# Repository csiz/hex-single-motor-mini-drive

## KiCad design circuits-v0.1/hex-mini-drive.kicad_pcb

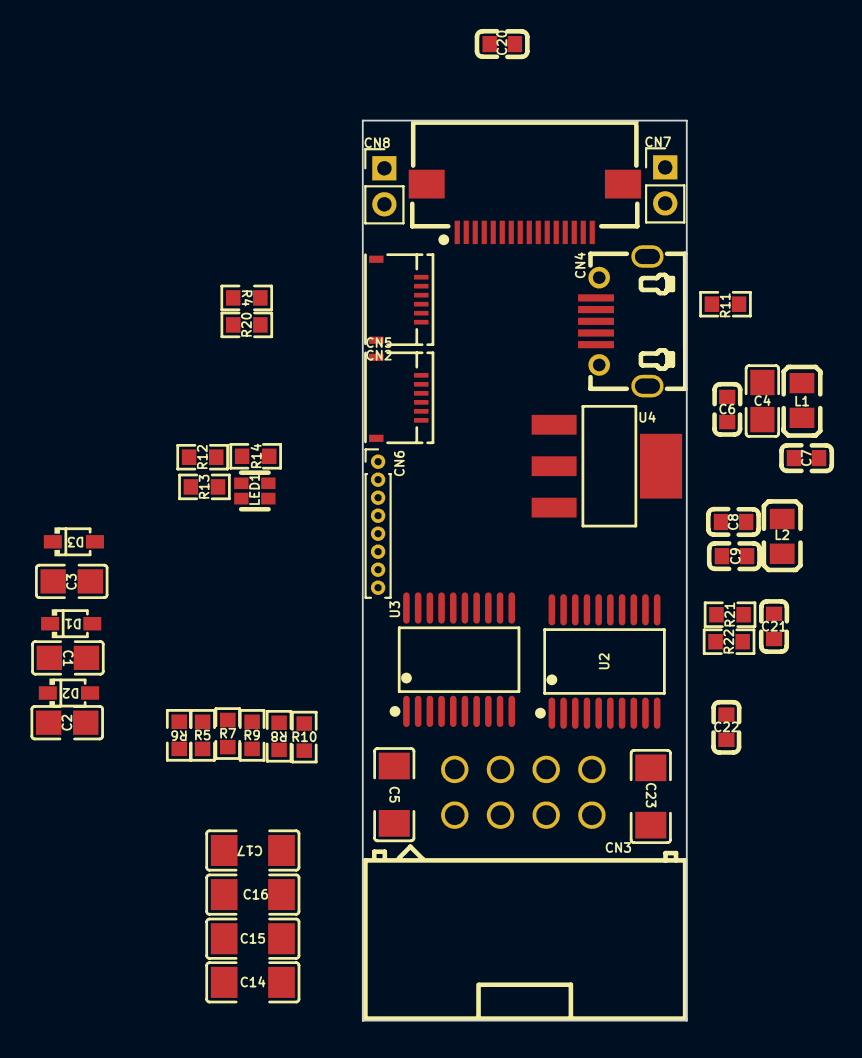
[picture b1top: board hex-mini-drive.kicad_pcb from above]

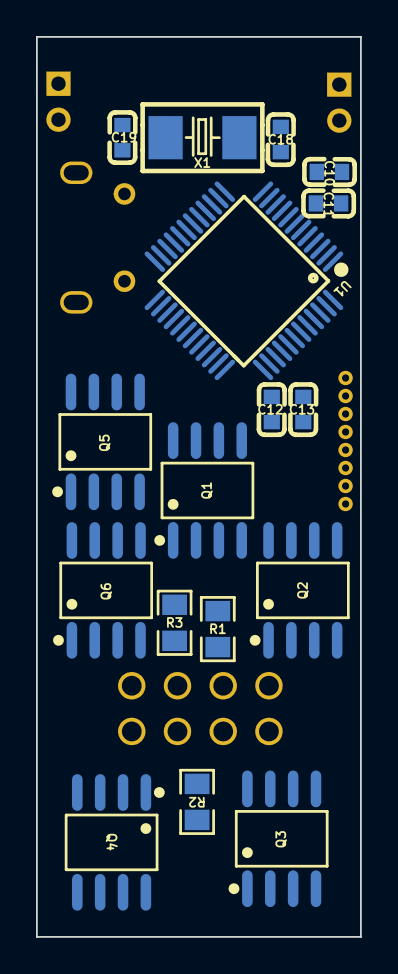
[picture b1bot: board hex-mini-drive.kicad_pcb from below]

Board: 4 copper layers, 18.0 x 50.0 mm, 65 parts (17 on the bottom side), 69 nets, no tracks yet.

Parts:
C1, C2, C3: 10nF; C0805
C4: 0.1uF; C0805
C5, C14, C15, C16, C17, C23: 10uF; C1206
C6, C7, C9: 1uF; C0603
C8, C10, C11, C12, C13, C20, C21, C22: 100nF; C0603
C18, C19: 30pF; C0603
CN1: FPC-SMD_P0.50-16P_FGS-XJ-H2.0
CN2, CN5: FPC-SMD_6P-P0.50_L3.8-W5.0
CN3: IDC-TH_8P-P2.54-H-R2-C4-S2.54
CN4: MICRO-USB-SMD_MICRONJ5P-1.0-1.25
CN6: Conn_01x08_Pin; PinHeader_1x08_P1.00mm_Vertical
CN7, CN8: Conn_01x02_Pin; PinHeader_1x02_P2.00mm_Vertical
D1, D2, D3: IN4148WS T4 SOD-323_L1.8-W1.3-LS2.5-RD
L1: 300mΩ; L0805
L2: 10uH; L0805
LED1: LED-ARRAY-SMD_4P-L1.6-W1.5-BR_XL-1615RGBC-RF
Q1, Q2, Q3, Q4, Q5, Q6: AO4266E SOIC-8_L4.9-W3.9-P1.27-LS6.0-BL
R1, R2, R3: 500mW 10mΩ; R0805
R4: 100kΩ; R0603
R5, R6, R7, R8, R9, R10: 10Ω; R0603
R11, R12, R13, R14: 1.5kΩ; R0603
R20: 10kΩ; R0603
R21, R22: 47kΩ; R0603
U1: STM32F103C8T6 LQFP-48_L7.0-W7.0-P0.50-LS9.0-BL
U2: INA4181A1 TSSOP-20_L6.5-W4.4-P0.65-LS6.4-BL
U3: FD6288T TSSOP-20_L6.5-W4.4-P0.65-LS6.4-BL
U4: AMS1117-3.3 SOT-223-3_L6.5-W3.4-P2.30-LS7.0-BR
X1: CRYSTAL-SMD_L5.0-W3.2

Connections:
+3V3: C6.2, C10.2, C11.2, C12.2, C13.2, C22.2, CN2.1, CN3.5, CN5.1, L2.1, LED1.2 (COM+), R11.2, U1.1 (VBAT), U1.24 (VDD_1), U1.36 (VDD_2), U1.48 (VDD_3), U2.5 (VS), U4.2 (VOUT)
+3V3A: C8.2, C9.2, L2.2, R21.2, U1.9 (VDDA)
+5V: CN1.1, CN4.1 (VCC), L1.2
+VDC: C4.2, C5.2, C14.1, C15.1, C16.1, C17.1, C23.1, CN1.12, CN1.13, CN1.14, CN1.15, CN1.16, CN7.2, CN8.2, D1.2 (A), D2.2 (A), D3.2 (A), Q1.5 (D), Q1.6 (D), Q1.7 (D), Q1.8 (D), Q3.5 (D), Q3.6 (D), Q3.7 (D), Q3.8 (D), Q5.5 (D), Q5.6 (D), Q5.7 (D), Q5.8 (D), R4.2, U3.7 (VCC)
/Boost Gate 1: C1.2, D1.1 (K), U3.20 (VB1)
/Boost Gate 2: C2.2, D2.1 (K), U3.17 (VB2)
/Boost Gate 3: C3.2, D3.1 (K), U3.14 (VB3)
/Filtered +5V: C7.2, L1.1, U4.3 (VIN)
/HO1: R5.1, U3.19 (HO1)
/HO2: R9.1, U3.16 (HO2)
/HO3: R10.1, U3.13 (HO3)
/LO1: R6.1, U3.11 (LO1)
/LO2: R7.2, U3.10 (LO2)
/LO3: R8.2, U3.9 (LO3)
/RCC_OSC_IN: C18.2, U1.5 (PD0-OSC_IN), X1.1 (OSC1)
/RCC_OSC_OUT: C19.2, U1.6 (PD1-OSC_OUT), X1.2 (OSC2)
ADC1_IN2: U1.12 (PA2), U2.2 (OUT1)
ADC1_IN3: U1.13 (PA3), U2.8 (OUT2)
ADC1_IN4: U1.14 (PA4), U2.13 (OUT3)
ADC1_IN5/REF: C21.2, R21.1, R22.2, U1.15 (PA5), U2.1 (REF1), U2.9 (REF2), U2.12 (REF3), U2.20 (REF4)
ADC1_IN6: R4.1, R20.2, U1.16 (PA6)
BOOT0: CN1.5, U1.44 (BOOT0)
GATE1H: Q1.4 (G), R5.2
GATE1L: Q2.4 (G), R6.2
GATE2H: Q3.4 (G), R9.2
GATE2L: Q4.4 (G), R7.1
GATE3H: Q5.4 (G), R10.2
GATE3L: Q6.4 (G), R8.1
GND: C4.1, C5.1, C6.1, C7.1, C8.1, C9.1, C10.1, C11.1, C12.1, C13.1, C14.2, C15.2, C16.2, C17.2, C18.1, C19.1, C20.1, C21.1, C22.1, C23.2, CN1.7, CN1.8, CN1.9, CN1.10, CN1.11, CN2.2, CN3.4, CN4.5 (GND), CN5.2, CN6.1, CN7.1, CN8.1, Q2.1 (S), Q2.2 (S), Q2.3 (S), Q4.1 (S), Q4.2 (S), Q4.3 (S), Q6.1 (S), Q6.2 (S), Q6.3 (S), R20.1, R22.1, U1.8 (VSSA), U1.23 (VSS_1), U1.35 (VSS_2), U1.47 (VSS_3), U2.16 (GND), U3.8 (COM), U4.1 (GND)
GPIO_Input_A: CN5.5, CN6.6, U1.2 (PC13-TAMPER-RTC)
GPIO_Input_B: CN5.6, CN6.7, U1.3 (PC14-OSC32_IN)
GPIO_Input_C: CN6.8, U1.4 (PC15-OSC32_OUT)
GPIO_Input_CS: CN1.4, U1.20 (PB2)
I2C1_SCL: CN5.4, U1.45 (PB8)
I2C1_SDA: CN5.3, U1.46 (PB9)
NRST: C20.2, CN1.6, U1.7 (NRST)
unnamed: LED1.3 (B-), R13.2
unnamed: LED1.4 (G-), R12.2
unnamed: LED1.1 (R-), R14.1
OUT1: C1.1, CN3.6, R1.2, U2.4 (IN+1), U3.18 (VS1)
OUT2: C2.1, CN3.7, R2.2, U2.7 (IN±2), U3.15 (VS2)
OUT3: C3.1, CN3.8, R3.2, U2.15 (IN+3), U3.12 (VS3)
SHUNT1: Q1.1 (S), Q1.2 (S), Q1.3 (S), Q2.5 (D), Q2.6 (D), Q2.7 (D), Q2.8 (D), R1.1, U2.3 (IN±1)
SHUNT2: Q3.1 (S), Q3.2 (S), Q3.3 (S), Q4.5 (D), Q4.6 (D), Q4.7 (D), Q4.8 (D), R2.1, U2.6 (IN+2)
SHUNT3: Q5.1 (S), Q5.2 (S), Q5.3 (S), Q6.5 (D), Q6.6 (D), Q6.7 (D), Q6.8 (D), R3.1, U2.14 (IN±3)
SPI2MISO: CN2.4, U1.27 (PB14)
SPI2_MOSI: CN2.3, U1.28 (PB15)
SPI2_NSS: CN2.6, U1.25 (PB12)
SPI2_SCK: CN2.5, U1.26 (PB13)
SYS_JTCK-SWCLK: CN6.4, U1.37 (PA14)
SYS_JTDI: CN6.3, U1.38 (PA15)
SYS_JTDO-TRACESWO: CN6.2, U1.39 (PB3)
SYS_JTMS-SWDIO: CN6.5, U1.34 (PA13)
TIM1_CH1: U1.29 (PA8), U3.1 (HIN1)
TIM1_CH1N: U1.17 (PA7), U3.4 (LIN1)
TIM1_CH2: U1.30 (PA9), U3.2 (HIN2)
TIM1_CH2N: U1.18 (PB0), U3.5 (LIN2)
TIM1_CH3: U1.31 (PA10), U3.3 (HIN3)
TIM1_CH3N: U1.19 (PB1), U3.6 (LIN3)
TIM2_CH1/H1: CN3.1, U1.10 (PA0-WKUP)
TIM2_CH2/H2: CN3.2, U1.11 (PA1)
TIM2_CH3/H3: CN3.3, U1.21 (PB10)
TIM2_CH4: R12.1, U1.22 (PB11)
TIM3_CH1: R13.1, U1.40 (PB4)
TIM3_CH2: R14.2, U1.41 (PB5)
USART1_RX: CN1.3, U1.43 (PB7)
USART1_TX: CN1.2, U1.42 (PB6)
USB_D+: CN4.3 (D+), R11.1, U1.33 (PA12)
USB_D-: CN4.2 (D-), U1.32 (PA11)

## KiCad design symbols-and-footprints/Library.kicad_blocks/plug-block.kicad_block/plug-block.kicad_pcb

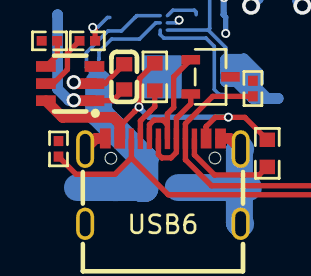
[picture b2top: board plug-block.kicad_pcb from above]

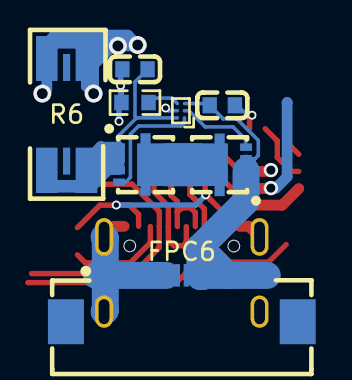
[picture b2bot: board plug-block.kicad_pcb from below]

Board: 4 copper layers, 18 parts (8 on the bottom side), 17 nets.

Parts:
C40, C80, C81: 1uF; C0603
D11: SOT-23-3_L3.0-W1.7-P0.95-LS2.9-BR
FPC6: FPC-SMD_20P-P0.50_XUNPU_FPC-05F-20PH20
Q19, Q20: WDFN-5_L3.1-W3.1-P0.65-BL_1
R6: 5mΩ; R2512 Shunt with Kelvin connections
R70: 20kΩ; R0402
R71, R89: 56kΩ; R0603
R75: 10kΩ; R0603
R91: 100kΩ; R0402
R101, R108: 1MΩ; R0402
U31: WLCSP-6_L1.2-W0.8-P0.40-TL
U32: SOT-23-6_L2.9-W1.6-P0.95-LS2.8-BR
USB6: USB-C-SMD_TYPE-C16PIN

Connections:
5V: C40.2, U32.1 (IN)
/servo-usb-connector5/CC1x: R71.2, USB6.A5 (CC1)
/servo-usb-connector5/CC2x: R89.1, USB6.B5 (CC2)
/servo-usb-connector5/ILIMx: R70.2, U32.5 (ILIM)
/servo-usb-connector5/VBUSx: R71.1, R89.2, U32.6 (OUT), USB6.A4B9 (VBUS), USB6.B4A9 (VBUS)
/servo-usb-connector5/VCCx: C80.2, FPC6.11, FPC6.12, FPC6.13, FPC6.14, FPC6.15, FPC6.16, FPC6.17, FPC6.18, FPC6.19, FPC6.20, Q19.1 (S), Q19.2 (S), Q19.3 (S), U31.C1 (VOUT)
/servo-usb-connector5/back-to-back-mosfets3/GATE1x: Q20.4 (G), U31.A1 (VGATE1)
/servo-usb-connector5/back-to-back-mosfets3/GATE2x: Q19.4 (G), U31.B1 (VGATE2)
/servo-usb-connector5/back-to-back-mosfets3/Mid-MOSFETSx: Q19.5 (D), Q20.5 (D)
/servo-usb-connector5/back-to-back-mosfets3/VIN: C81.2, Q20.1 (S), Q20.2 (S), Q20.3 (S), R6.1 (Shunt-1), U31.A2 (VIN)
CONNECTx: R75.2, U31.C2 (VCT)
GND: C40.1, C80.1, C81.1, D11.3 (K), FPC6.1, FPC6.2, FPC6.3, FPC6.4, FPC6.5, FPC6.6, FPC6.7, FPC6.8, FPC6.9, FPC6.10, R70.1, R75.1, R101.1, R108.1, U31.B2 (GND), U32.2 (GND), USB6.1 (SHELL), USB6.2 (SHELL), USB6.3 (SHELL), USB6.4 (SHELL), USB6.A1B12 (GND), USB6.B1A12 (GND)
SERVO6_BOOT0: R108.2, USB6.A8 (SBU1)
SERVO6_NRST: R101.2, USB6.B8 (SBU2)
USBDN6_D+: D11.2 (A1), USB6.A6 (DP1), USB6.B6 (DP2)
USBDN6_D-: D11.1 (A1), USB6.A7 (DN1), USB6.B7 (DN2)
nOCS6: R91.2, U32.4 (/FAULT)
